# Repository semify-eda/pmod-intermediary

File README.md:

# PMOD™ Intermediary - Monitoring and debugging PMOD™ peripherals

## Overview

Our PMOD™ intermediary board is designed for monitoring and debugging purposes, allowing users to monitor all signals of a 12-pin PMOD™ connector.
With this board, debugging connection problems with an existing PMOD™ extension board becomes an easy task.
A green LED, which is integrated into the board, provides a quick and easy way to check the presence of the supply voltage (VCC).

In addition, the board enables users to measure the actual current consumption.
This can be done by either adding an ampere meter in series or measuring the voltage drop across the integrated shunt resistors.

Each power and ground line of the 12-pin PMOD™ connector can be individually measured.

The size and pinout of our PMOD™ intermediary board follow the Digilent Pmod™ Interface Specification, ensuring compatibility with a wide range of devices. With this board, users can easily monitor and debug PMOD™ devices without the need for additional hardware or complex set-ups.

## Current measurement

Are you aware of the current consumption of your PMOD™ board?

It is crucial to know the current consumption of your PMOD™ peripheral board, especially if it approaches the limits of the host power supply. The PMOD™ Intermediary board offers two ways to measure the current consumption.

The PMOD™ intermediary provides four current consumption measurement points.

  | Pin  | Signal |
  | ---- | ------ |
  | 5    | GND  |
  | 6    | VCC  |
  | 11   | GND  |
  | 12   | VCC  |

### Average current using an ampere meter
To measure the average power consumption, simply remove the corresponding jumper and connect an ampere between pin 1 and pin 2. This allows for an accurate measurement of the current drawn by the PMOD™ device.

THe current can be measured in the VCC as well as in the GND path.

### Dynamic current using shunt resistor
To measure the dynamic power consumption of the PMOD™ device, insert the shunt resistor into the supply (VCC) or ground (GND) line. This can be achieved by shorting pin 2 and pin 3 of the corresponding header with a jumper. The current can then be calculated by measuring the voltage drop across the shunt resistor. This allows for an accurate measurement of the dynamic current drawn by the connected PMOD™ peripheral.

The shunf resistor has a value of 100mOhm.

$I = U / R $

A voltage drop of 100mV corresponds to a current of $I = 0.1 / 0.1 = 1A $.

To avoid any impact of the voltage drop across the shunt resistor during normal operation it is recommended to short the shunt resistor. This can be achieved by shorting pin 1 and pin 2 of the corresponding header with a jumper.

## External supply voltage

By removing the jumper and connecting an external power supply to the VCC header pin 1, the PMOD™ can be powered using an external power source.

**Caution** When using an external power supply, it is important to take precautions to avoid exceeding the allowed voltage ranges of the connected devices of the PMOD™ host and peripherals.

## Reference

  - [Schemtaic](https://github.com/semify-eda/pmod-intermediary/blob/main/pmod-intermediary.pdf)
  - [Digilent Pmod™ Interface Specification](https://digilent.com/reference/_media/reference/pmod/digilent-pmod-interface-specification.pdf)

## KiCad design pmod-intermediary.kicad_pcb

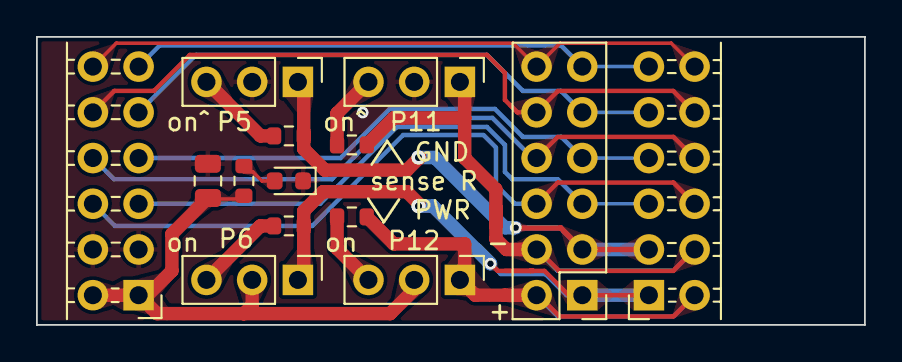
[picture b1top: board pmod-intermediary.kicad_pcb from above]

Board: 2 copper layers, 46.0 x 16.0 mm, 14 parts (0 on the bottom side), 19 nets.

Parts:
C1: 22u; C_0805_2012Metric
D1: 0603_LED_Green; LED_0603_1608Metric
J1: Conn_02x06_male_plug; PinHeader_2x06_P2.54mm_Horizontal
J2: Conn_02x06_pins; PinHeader_2x06_P2.54mm_Vertical
J3: Conn_02x06_female_receptable; PinSocket_2x06_P2.54mm_Horizontal
J4, J5, J6, J8: Conn_01x03; PinHeader_1x03_P2.54mm_Vertical
R1, R2, R3, R4: R_sense; R_0603_1608Metric
R5: 22k; R_0603_1608Metric

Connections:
/in_1: J1.12, J2.12, J3.12
/in_2: J1.10, J2.10, J3.10
/in_3: J1.8, J2.8, J3.8
/in_4: J1.6, J2.6, J3.6
/in_7: J1.11, J2.11, J3.11
/in_8: J1.9, J2.9, J3.9
/in_9: J1.7, J2.7, J3.7
/in_10: J1.5, J2.5, J3.5
/in_gnd: C1.2, D1.1 (K), J1.3, J1.4, J4.2, J6.2
/in_pwr: C1.1, J1.1, J1.2, J5.2, J8.2, R5.2
/out_gnd_5: J2.4, J3.4, J6.1, R3.2
/out_gnd_11: J2.3, J3.3, J4.1, R1.2
/out_pwr_6: J2.2, J3.2, J8.1, R4.2
/out_pwr_12: J2.1, J3.1, J5.1, R2.2
unnamed: D1.2 (A), R5.1
unnamed: J4.3, R1.1
unnamed: J5.3, R2.1
unnamed: J6.3, R3.1
unnamed: J8.3, R4.1

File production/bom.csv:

Designator,Footprint,Quantity,Value,LCSC Part #
C1,0805,1,22u,C45783
D1,0603,1,0603_LED_Green,C72043 
J1,PinHeader_2x06_P2.54mm_Horizontal,1,Conn_02x06_male_plug,
J2,PinHeader_2x06_P2.54mm_Vertical,1,Conn_02x06_pins,
J3,PinSocket_2x06_P2.54mm_Horizontal,1,Conn_02x06_female_receptable,
"J4, J5, J6, J8",PinHeader_1x03_P2.54mm_Vertical,4,Conn_01x03,
R1,0603,1,R_sense,C22936
R2,0603,1,R_sense,C22936
R3,0603,1,R_sense,C22936
R4,0603,1,R_sense,C22936
R5,0603,1,22k,C31850

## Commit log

2023-03-30 production files, pdf
2023-10-25 Create CNAME
2023-10-25 Rename pmod--intermediary.md to pmod-intermediary.md
2023-10-25 Update SmartWave_Control_Datasheet.md
    Added info
2023-10-25 Update SmartWave_Control_Datasheet.md
    Updates
2023-10-27 Added SmartWave_Blockdiagram_Pins.drawio.svg
2023-10-27 Added SmartWave_Blockdiagram.drawio.svg
2023-10-27 Added SmartWave_Blockdiagram-Pin.drawio.svg
2023-10-27 Rename SmartWave_Blockdiagram-Pin.drawio.svg to SmartWave_Blockdiagram_Pin.drawio.svg
2023-10-27 Rename SmartWave_Blockdiagram_Pin.drawio.svg to SmartWave_Blockdiagram_Pin.svg
